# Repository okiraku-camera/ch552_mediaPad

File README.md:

# CH552 MediaPad

English version: [README_en.md](README_en.md)

CH552G マイクロコントローラを使ったUSB HID マクロパッド（2x4キー + エンコーダ搭載）です。WebHID を使ってキーマップをリアルタイムで設定・変更できます。

## フォルダ構成

- **`pcb/`**: KiCAD 8 による基板設計（回路図、PCB）
- **`plates/`**: レーザーカット用アクリルプレート設計
- **`mediaPad/`**: Arduino ファームウェア（CH552G 向け）
- **`html/`**: WebHID 設定用ブラウザアプリ（HTML/CSS/JavaScript）
- **`LICENSE`**: プロジェクトライセンス

## ハードウェア

- **マイコン**: CH552G
- **キー**: 8キー（2x4 レイアウト）
- **エンコーダ**: 1個
- **トッププレート**: 5mm アクリル（透明）
- **ミドルプレート**: 5mm アクリル（マット透明）
- **ボトムプレート**: 2mm アクリル（透明）
- **USB**: USB Type-C コネクタ

詳細は [pcb/README.md](pcb/README.md)・[plates/README.md](plates/README.md) をご覧ください。

## ソフトウェア

### ファームウェア (mediaPad/)
CH552G 向けの Arduino スケッチ。USB HID キーボード・メディア操作・エンコーダ入力に対応しています。

### Web アプリ (html/)
ブラウザから **WebHID** 経由でデバイスと通信し、キーマップの読み書きや設定変更ができるアプリケーションです。(ch552_mediaPad.html)

## ライセンス

このプロジェクトはハードウェアとソフトウェアから構成されています。

Copyright (c) Takeshi Higasa, okiraku-camera.tokyo

詳細は [LICENSE](./LICENSE) をご覧ください。

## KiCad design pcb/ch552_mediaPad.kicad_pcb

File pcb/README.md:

# PCB (ch552_mediaPad)

このディレクトリには、CH552 MediaPad の KiCad 設計データ（回路図・基板レイアウト）が含まれています。

## 使用ツール

- KiCad 8.0

## 含まれる主なファイル

- `ch552_mediaPad.kicad_sch` : 回路図
- `ch552_mediaPad.kicad_pcb` : PCB レイアウト
- `ch552_mediaPad.kicad_pro` : プロジェクト設定
- `local/` : この PCB のためのフットプリントライブラリ

### local/ ディレクトリの内容

- `Hole_M3_SmallPad.kicad_mod` : M3 取り付け穴
- `MX_PCB_1.25u.kicad_mod` : 1.25u キースイッチ用フットプリント
- `MX_Plate_hole.kicad_mod` : MX スイッチ用フットプリントと置き換えて、スイッチプレートを設計するためのフットプリント
- `SW_Cherry_MX_PCB_RE_1.25u.kicad_mod` : MX 1.25U とロータリーエンコーダー EC-12 を組み合わせたフットプリント
- `USB_C_Receptacle_304J-BCP16.kicad_mod` : USB Type-C コネクタ

## メモ

- 共同作業時は、編集対象（回路図/PCB）と合わせて関連設定ファイルの差分も確認してください。

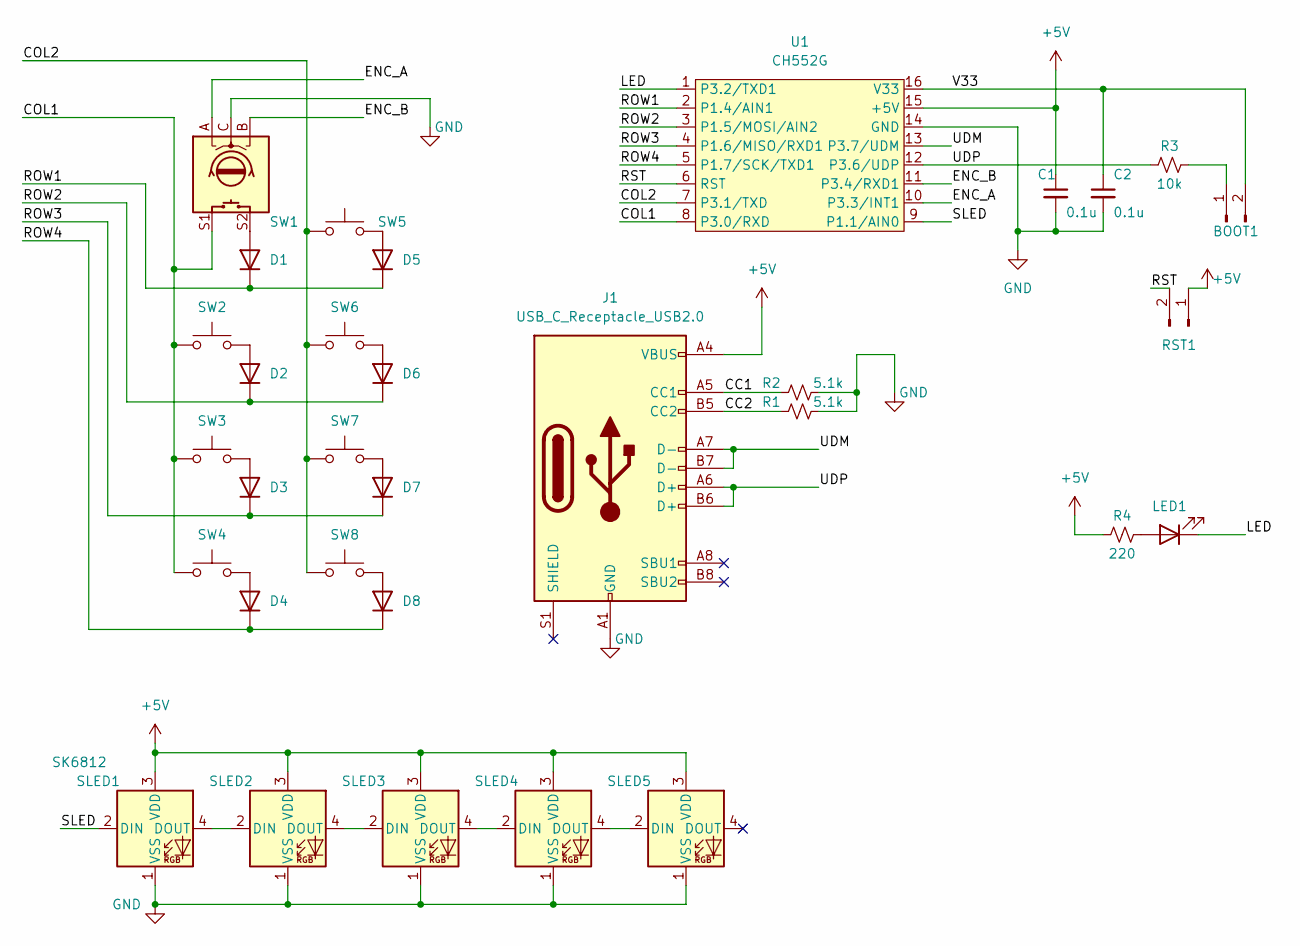
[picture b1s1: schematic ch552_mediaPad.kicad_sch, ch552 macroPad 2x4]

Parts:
BOOT1: Conn_01x02_Male; PinHeader_1x02_P2.54mm_Vertical
C1, C2: 0.1u; C_0603_1608Metric
D1, D2, D3, D4, D5, D6, D7, D8: 1N4148W; D_SOD-123
J1: USB_C_Receptacle_USB2.0; USB_C_Receptacle_304J-BCP16
LED1: LED; LED_1206_3216Metric_Pad1.42x1.75mm_HandSolder
R1, R2: 5.1k; R_0402_1005Metric
R3: 10k; R_0402_1005Metric
R4: 220; R_0402_1005Metric
RST1: Conn_01x02_Male; PinHeader_1x02_P2.54mm_Vertical
SLED1, SLED2, SLED3, SLED4, SLED5: SK6812; LED_SK6812_PLCC4_5.0x5.0mm_P3.2mm
SW1: RotaryEncoder_Switch; SW_Cherry_MX_PCB_RE_1.25u
SW2, SW3, SW4, SW5, SW6, SW7, SW8: SW_Push; MX_PCB_1.25u
U1: CH552G; SOP-16_3.9x9.9mm_P1.27mm

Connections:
+5V: C1.1, J1.A4 (VBUS), J1.A9 (VBUS), J1.B4 (VBUS), J1.B9 (VBUS), R4.1, RST1.1, SLED1.3 (VDD), SLED2.3 (VDD), SLED3.3 (VDD), SLED4.3 (VDD), SLED5.3 (VDD), U1.15 (+5V)
/CC1: J1.A5 (CC1), R2.1
/CC2: J1.B5 (CC2), R1.1
/COL1: SW1.S1, SW2.1, SW3.1, SW4.1, U1.8 (P3.0/RXD)
/COL2: SW5.1, SW6.1, SW7.1, SW8.1, U1.7 (P3.1/TXD)
/ENC_A: SW1.A, U1.10 (P3.3/INT1)
/ENC_B: SW1.B, U1.11 (P3.4/RXD1)
/LED: LED1.1 (K), U1.1 (P3.2/TXD1)
/ROW1: D1.1 (K), D5.1 (K), U1.2 (P1.4/AIN1)
/ROW2: D2.1 (K), D6.1 (K), U1.3 (P1.5/MOSI/AIN2)
/ROW3: D3.1 (K), D7.1 (K), U1.4 (P1.6/MISO/RXD1)
/ROW4: D4.1 (K), D8.1 (K), U1.5 (P1.7/SCK/TXD1)
/RST: RST1.2, U1.6 (RST)
/SLED: SLED1.2 (DIN), U1.9 (P1.1/AIN0)
/UDM: J1.A7 (D-), J1.B7 (D-), U1.13 (P3.7/UDM)
/UDP: J1.A6 (D+), J1.B6 (D+), R3.1, U1.12 (P3.6/UDP)
/V33: BOOT1.2, C2.1, U1.16 (V33)
GND: C1.2, C2.2, J1.A1 (GND), J1.A12 (GND), J1.B1 (GND), J1.B12 (GND), R1.2, R2.2, SLED1.1 (VSS), SLED2.1 (VSS), SLED3.1 (VSS), SLED4.1 (VSS), SLED5.1 (VSS), SW1.C, U1.14 (GND)
unnamed: BOOT1.1, R3.2
unnamed: D1.2 (A), SW1.S2
unnamed: D2.2 (A), SW2.2
unnamed: D3.2 (A), SW3.2
unnamed: D4.2 (A), SW4.2
unnamed: D5.2 (A), SW5.2
unnamed: D6.2 (A), SW6.2
unnamed: D7.2 (A), SW7.2
unnamed: D8.2 (A), SW8.2
unnamed: LED1.2 (A), R4.2
unnamed: SLED1.4 (DOUT), SLED2.2 (DIN)
unnamed: SLED2.4 (DOUT), SLED3.2 (DIN)
unnamed: SLED3.4 (DOUT), SLED4.2 (DIN)
unnamed: SLED4.4 (DOUT), SLED5.2 (DIN)

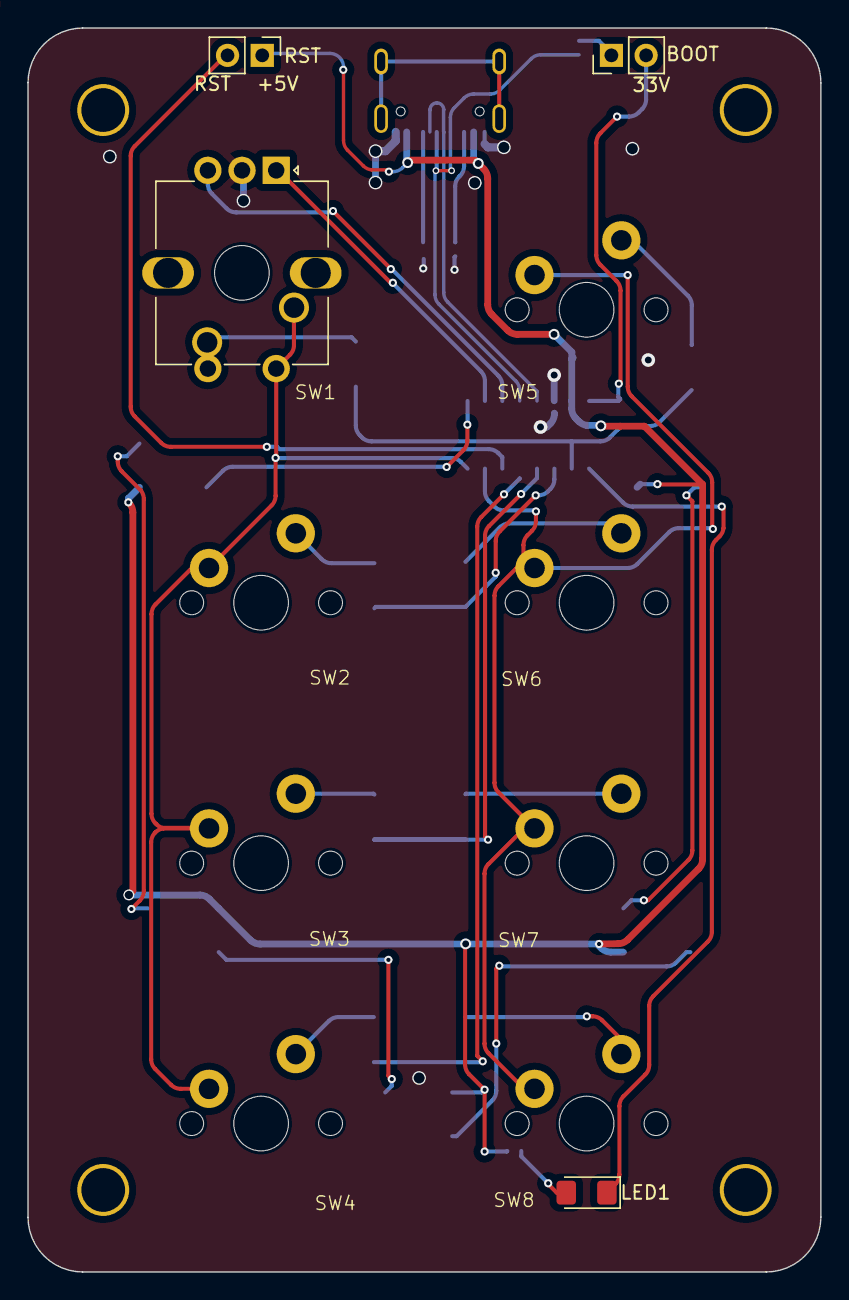
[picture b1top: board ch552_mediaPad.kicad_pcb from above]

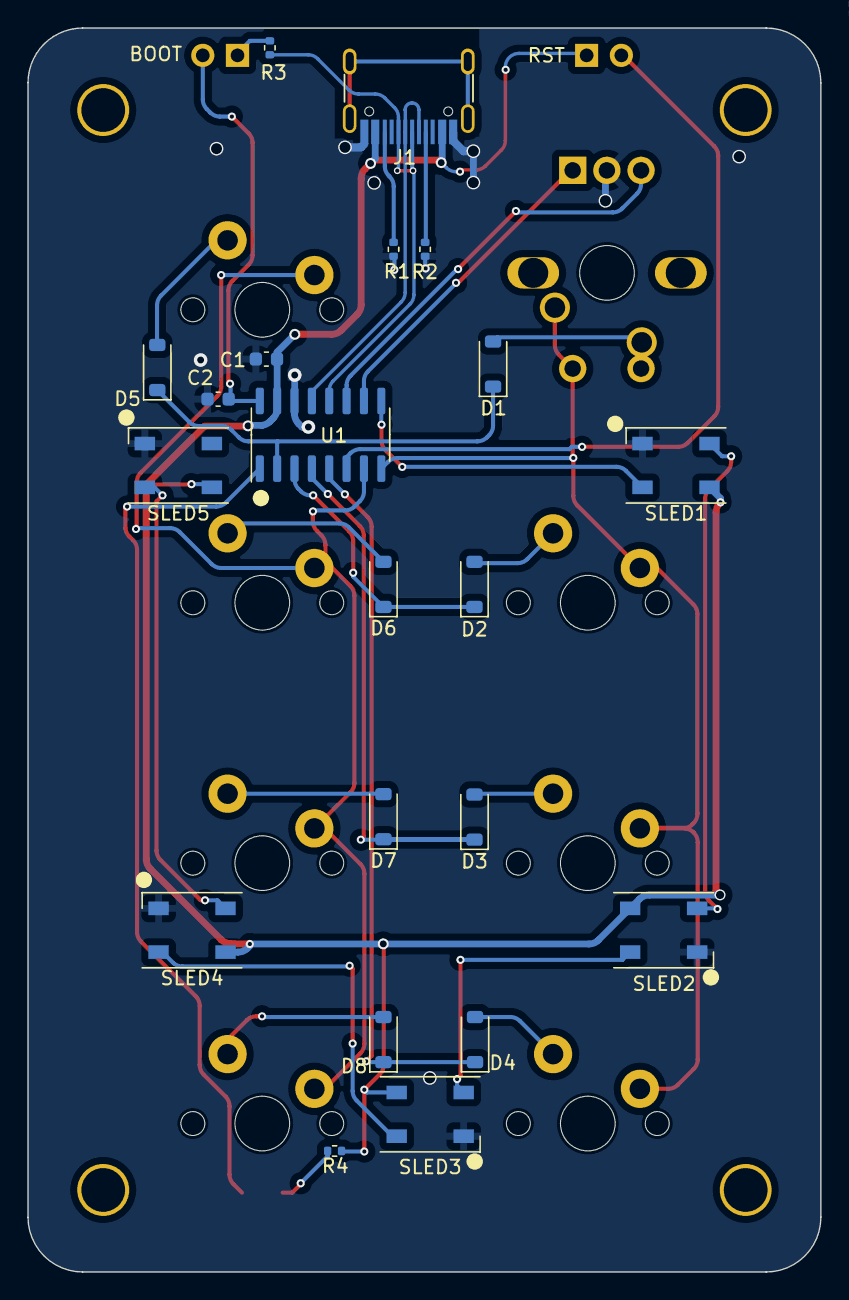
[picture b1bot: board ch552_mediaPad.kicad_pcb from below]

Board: 2 copper layers, 58.0 x 91.0 mm, 33 parts (21 on the bottom side), 32 nets.

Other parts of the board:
REF: Hole_M3_SmallPad

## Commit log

2026-04-02 hardware
2026-04-02 update documents
2026-04-04 change some keycodes. Add macro repeat codes, bug fix for modifier keys.
2026-04-04 Add macro repeat code. change some key codes.
2026-04-06 move to library and rename.
2026-04-06 Use buildPreferences to give instructions to the compiler.
2026-04-06 change encoder timing.
2026-04-06 update documents.
2026-04-06 update docs.
2026-04-07 html name
2026-04-11 Add READMEs for PCB.
